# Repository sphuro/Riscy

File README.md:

# RISCY

I am bulding a devboard using esp32-c3 for risc 5 architechture.

## Module

- esp32-c3 02 :-
  `https://robu.in/product/espressif-esp32-c3-wroom-02-n4-module/`

## USB slave to UART

- usb to uart link x1:-
  `https://robu.in/product/ft231xs-usb-to-full-handshake-uart-ic/`
- usb c 3.1 female buy link x1 :-
  `https://sharvielectronics.com/product/16-pin-c-type-usb-connector-smd-package/`

### Automatic Bootloader mechanism

- here is the blog covering this topic:
  `https://medium.com/@kazutaka.yoshinaga/esp32-understanding-the-automatic-boot-loader-mechanism-and-truth-table-68c4dcfd081b`
- BJT link x2 :-
  `https://robu.in/product/mmbt2222-npn-transistor-pack-of-15/`

## Reset and Boot buttons

### tact-switch-tvbp06-6-0x3-5mm

- 4 pin tactile switch x2 :-
  `https://sharvielectronics.com/product/6x6x6mm-4-pin-smd-push-button-switch-black-smd-package/?srsltid=AfmBOoqkUntN9e5Ccbb3nGcXEwSu-7Jxecq2lp09xIixMuHtoX-pbkdE`

## Programable LED

- link to buy x1 each:-
  - `https://robu.in/product/1206-surface-mount-led-white-50-pcs/`
  - `https://robu.in/product/0805-surface-mount-led-green-50-pcs/`
  - `https://robu.in/product/1210-surface-mount-led-red-50-pcs/`

## Voltage Regulator

- link to buy x1:-
  - `https://robu.in/product/ams1117-3-3v-1a-sot-223-voltage-regulator-ic-pack-of-5-ics/?gad_source=1&gclid=Cj0KCQiAhvK8BhDfARIsABsPy4iSbVYHEwlP9KEBU2B-lCpn-yx6If_Pfp03lKlFopRlRfcGBhBD0BAaAo5wEALw_wcB`

## Schematics

## Capacitors

- 47 pf (1206) x2
  `https://robu.in/product/1206cg470j102nt-fh-smd-multilayer-ceramic-capacitor-47-pf-1k-v-1206-3216-metric-%C2%B1-5-c0g-np0/`

- 1uf (0805) x1
  `https://robu.in/product/1uf-1000nf-50v-capacitor-0805-smd-package-pack-of-10/?gad_source=1&gclid=CjwKCAiAqfe8BhBwEiwAsne6gRW89rA8-Swm024kPMmwT7c9DuGJLPZeQFsVlMFR-OqpyiHtYQ1T4hoC8iMQAvD_BwE`

- 0.1uf (0603) x4
  `https://robu.in/product/0-1uf-capacitor-smdc-0603/?gad_source=1&gclid=CjwKCAiAqfe8BhBwEiwAsne6gWn9uzvhnW72vBLiLfLgH6g2IBu4aXkYyNnVniyPnGsfjDwM305cGxoC8nkQAvD_BwE`
- 10uf (0805) x1
  `https://robu.in/product/10uf-10000nf-25-v-capacitor-0805-smd-package-pack-of-10/?gad_source=1&gclid=CjwKCAiAqfe8BhBwEiwAsne6gSNCd9WapUePWtNVtayLgPHIMiImB_SQO5EiwIjBxiPgrBeaZvYwxxoCuBgQAvD_BwE`

- 22uf (0805) x2
  `https://robu.in/product/yageo-22uf-25v-electrolytic-capacitor-5-x-11mm/?gad_source=1&gclid=CjwKCAiAqfe8BhBwEiwAsne6gWyHPdNbx2DJMTqJMZTA1229QODbWIoOOmdcEkEg3BOqxQL2i1x2ehoCttgQAvD_BwE`

## Resistors

- 10k (1206) x3
  `https://robu.in/product/yageo-10k-ohm-1-4w-1206-surface-mount-chip-resistor-pack-of-50/?gad_source=1&gclid=CjwKCAiAqfe8BhBwEiwAsne6gZWv9w5e9PMNmgXxTNiYDh80E5rCTzmXLJArUMoy2vFAzwSFBDGwHRoCKAUQAvD_BwE`
- 2k (0603) x1
  `https://robu.in/product/rc0603fr-072kl-yageo-res-thick-film-0603-2k-ohm-1-0-1w1-10w-%C2%B1100ppm-c-pad-smd-t-r/?gad_source=1&gclid=CjwKCAiAqfe8BhBwEiwAsne6gWDPpM3FZ68ny4cKiBX4H2pzpEQgQKrVqhm_9OjcrVDXVOdlWZfx0RoCqCEQAvD_BwE`
- 5.1k (1206) x1
  `https://robu.in/product/rc1206fr-075k1l-yageo-res-thick-film-1206-5-1k-ohm-1-0-25w1-4w-%C2%B1100ppm-c-pad-smd-t-r/?gad_source=1&gclid=CjwKCAiAqfe8BhBwEiwAsne6gRqt6TucMgg01SNZ5VyACSfpWdVqewY8vab5gWvl6FbrrHuYexlRzxoCukMQAvD_BwE`
- 22k (1206) x3
  `https://robu.in/product/22k-ohm-1-4w-1206-surface-mount-chip-resistor-pack-of-100/?gad_source=1&gclid=CjwKCAiAqfe8BhBwEiwAsne6gS6hBlgg2iVJp858rXo21lLIIVadU-xK-fzI3kwSm3MWMYYFXDwUsBoCjh4QAvD_BwE`
- 27 (0805) x2
  `https://robu.in/product/rc0805fr-0727rl-yageo-smd-chip-resistor-27-ohm-%C2%B1-1-125-mw-0805-2012-metric-thick-film-general-purpose/`
- 1 (1206) x2
  `https://robu.in/product/1-ohm-1-4w-1206-surface-mount-chip-resistor-pack-of-100/?gad_source=1&gclid=CjwKCAiAqfe8BhBwEiwAsne6gYzLEAPAPqUGiqb02MYLoErwIDmVYmgq0LpQvgXpQUw6lDAnweQhTRoCmqYQAvD_BwE`

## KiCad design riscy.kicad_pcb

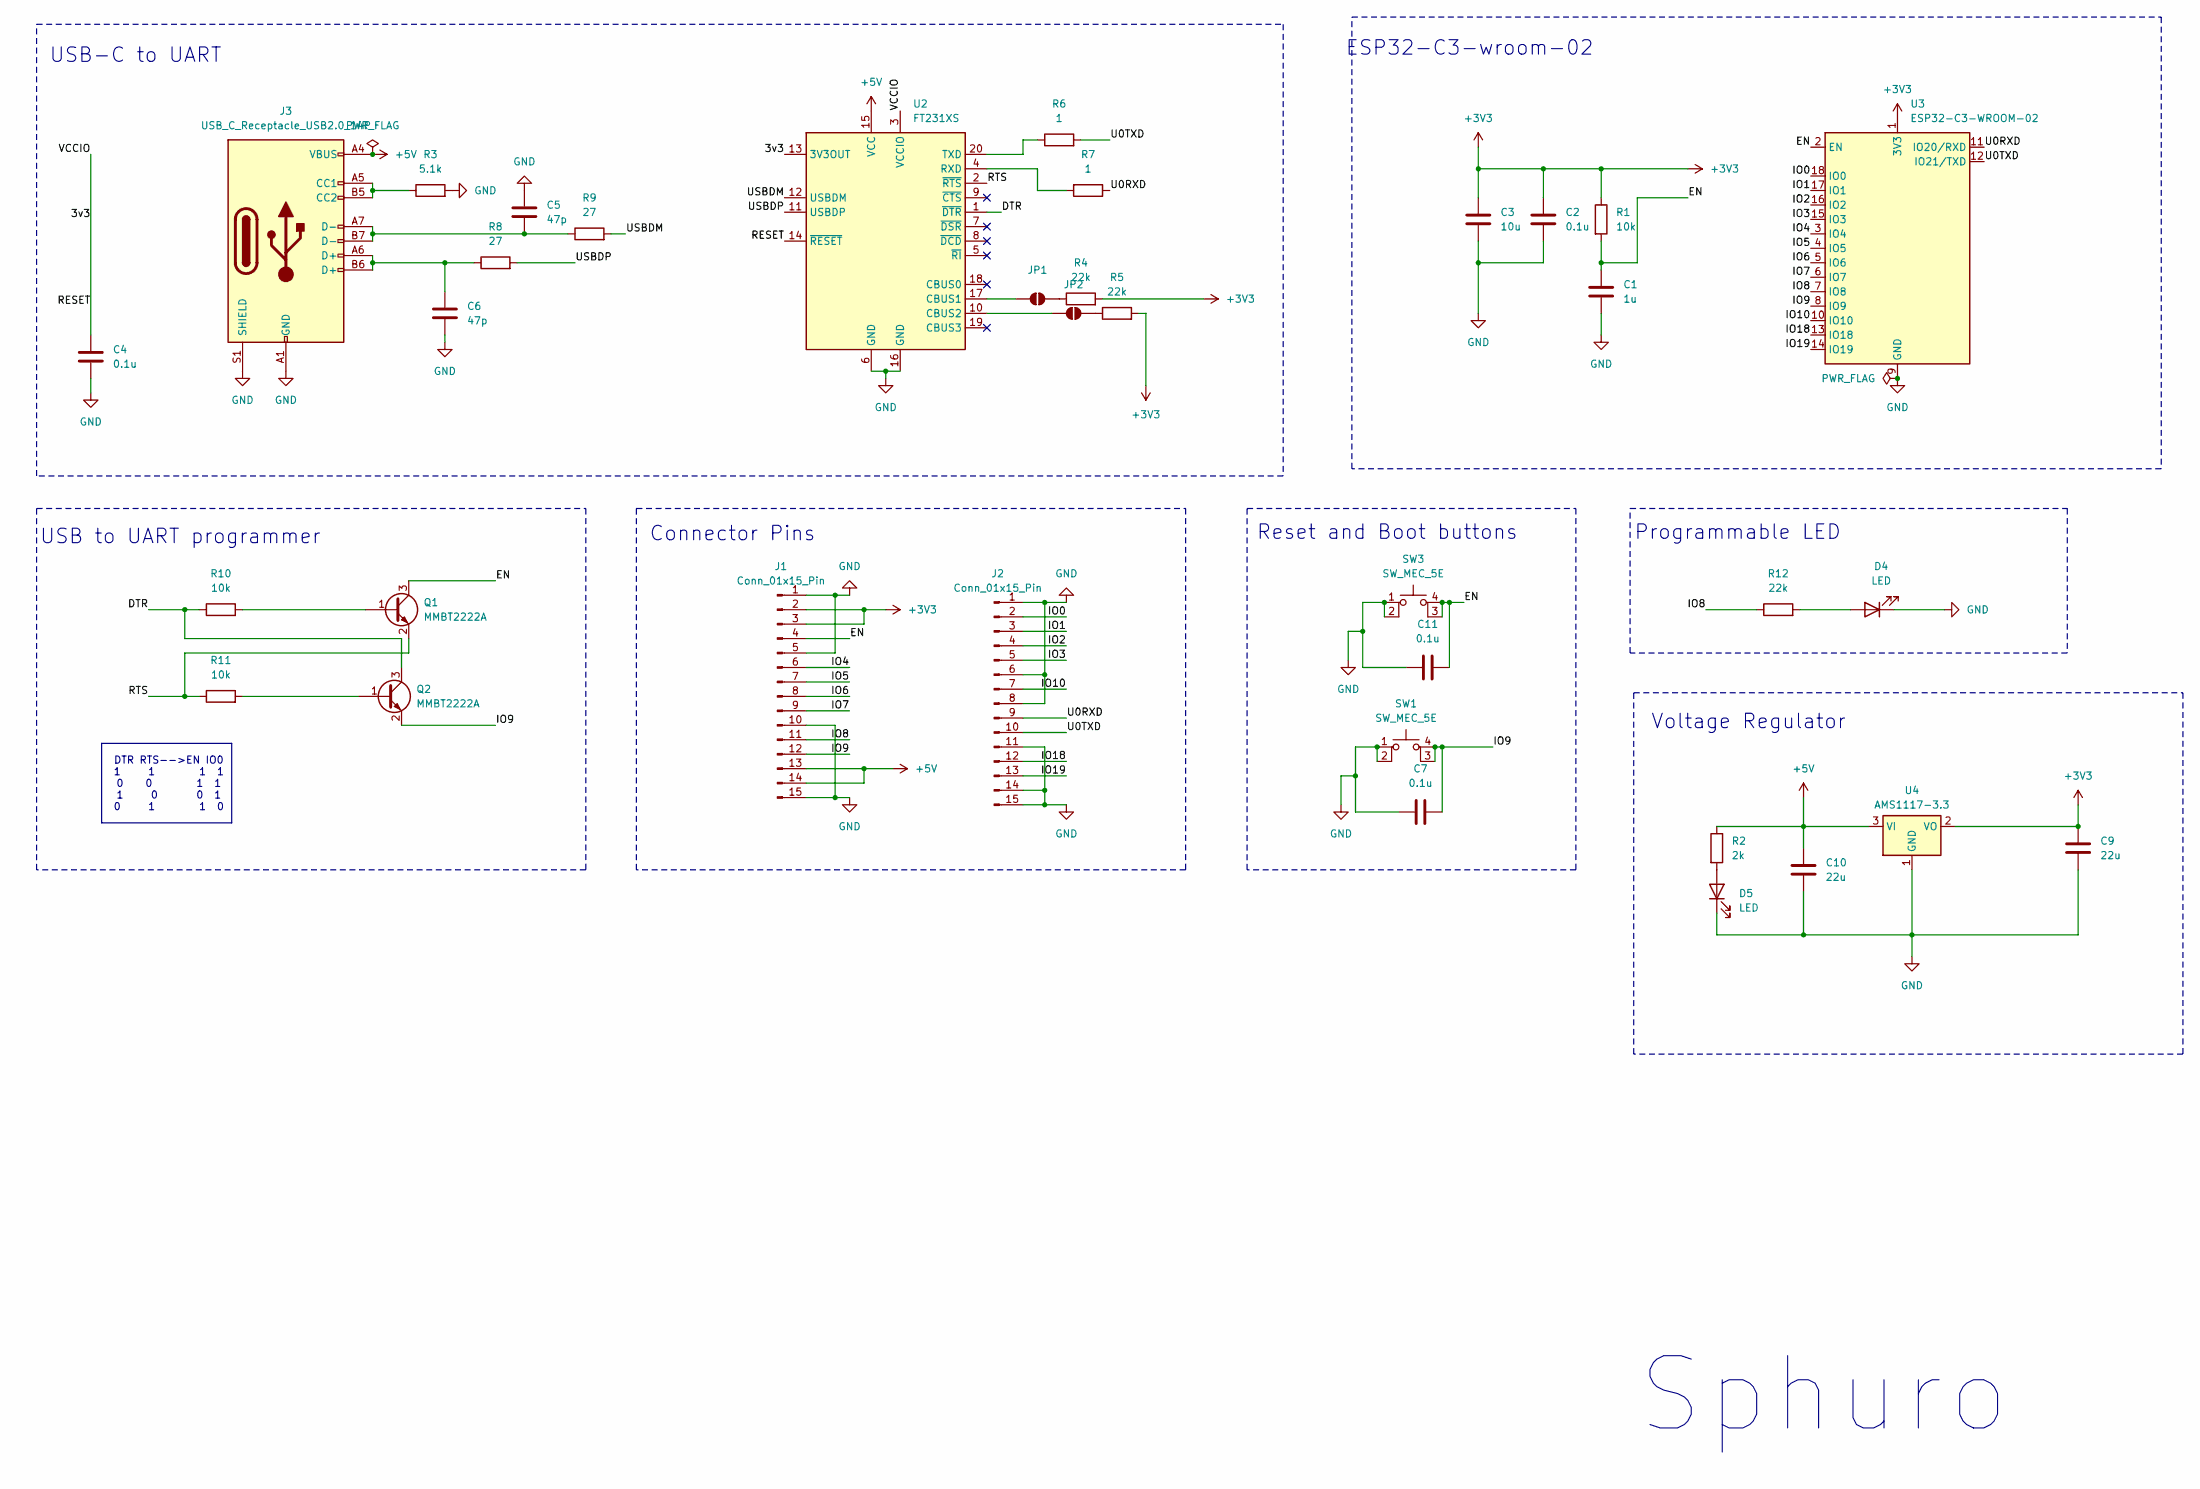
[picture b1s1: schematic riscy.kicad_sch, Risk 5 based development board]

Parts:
C1: 1u; C_0805_2012Metric
C2, C4, C7, C11: 0.1u; C_0603_1608Metric
C3: 10u; C_1206_3216Metric
C5, C6: 47p; C_1206_3216Metric
C9, C10: 22u; C_0805_2012Metric
D4: LED; LED_1206_3216Metric
D5: LED; LED_0805_2012Metric
J1, J2: Conn_01x15_Pin; PinHeader_1x15_P2.54mm_Vertical
J3: USB_C_Receptacle_USB2.0_14P; USB_C_Receptacle_GCT_USB4105-xx-A_16P_TopMnt_Horizontal
JP1, JP2: SolderJumper-2_P1.3mm_Open_RoundedPad1.0x1.5mm
Q1, Q2: MMBT2222A; SOT-23
R1, R10, R11: 10k; R_1206_3216Metric
R2: 2k; R_0603_1608Metric
R3: 5.1k; R_1206_3216Metric
R4, R5, R12: 22k; R_1206_3216Metric
R6, R7: 1; R_1206_3216Metric
R8, R9: 27; R_0805_2012Metric
SW1, SW3: SW_MEC_5E; SW_1825910-6-4
U2: FT231XS; SSOP-20_3.9x8.7mm_P0.635mm
U3: ESP32-C3-WROOM-02
U4: AMS1117-3.3; SOT-223-3_TabPin2

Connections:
+3V3: C2.1, C3.1, C9.1, J1.2, J1.3, R1.1, R4.2, R5.2, U3.1 (3V3), U4.2 (VO)
+5V: C10.1, J1.13, J1.14, J3.A4 (VBUS), J3.A9 (VBUS), J3.B4 (VBUS), J3.B9 (VBUS), R2.1, U2.15 (VCC), U4.3 (VI)
/3v3: C4.1, U2.3 (VCCIO), U2.13 (3V3OUT), U2.14 (~RESET)
/DTR: Q2.3 (C), R10.1, U2.1 (~DTR)
/EN: C1.1, C11.2, J1.4, Q1.3 (C), R1.2, SW3.3 (K), SW3.4 (A), U3.2 (EN)
/IO0: J2.2, U3.18 (IO0)
/IO1: J2.3, U3.17 (IO1)
/IO2: J2.4, U3.16 (IO2)
/IO3: J2.5, U3.15 (IO3)
/IO4: J1.6, U3.3 (IO4)
/IO5: J1.7, U3.4 (IO5)
/IO6: J1.8, U3.5 (IO6)
/IO7: J1.9, U3.6 (IO7)
/IO8: J1.11, R12.1, U3.7 (IO8)
/IO9: C7.2, J1.12, Q2.2 (E), SW1.3 (K), SW1.4 (A), U3.8 (IO9)
/IO10: J2.7, U3.10 (IO10)
/IO18: J2.12, U3.13 (IO18)
/IO19: J2.13, U3.14 (IO19)
/RTS: Q1.2 (E), R11.1, U2.2 (~RTS)
/U0RXD: J2.9, R7.1, U3.11 (IO20/RXD)
/U0TXD: J2.10, R6.2, U3.12 (IO21/TXD)
/USBDM: R9.2, U2.12 (USBDM)
/USBDP: R8.2, U2.11 (USBDP)
GND: C1.2, C2.2, C3.2, C4.2, C5.1, C6.2, C7.1, C9.2, C10.2, C11.1, D4.1 (K), D5.1 (K), J1.1, J1.5, J1.10, J1.15, J2.1, J2.6, J2.8, J2.11, J2.14, J2.15, J3.A1 (GND), J3.A12 (GND), J3.B1 (GND), J3.B12 (GND), J3.S1 (SHIELD), R3.2, SW1.1, SW1.2, SW3.1, SW3.2, U2.6 (GND), U2.16 (GND), U3.9 (GND), U3.19 (GND), U4.1 (GND)
unnamed: C5.2, J3.A7 (D-), J3.B7 (D-), R9.1
unnamed: C6.1, J3.A6 (D+), J3.B6 (D+), R8.1
unnamed: D4.2 (A), R12.2
unnamed: D5.2 (A), R2.2
unnamed: J3.A5 (CC1), J3.B5 (CC2), R3.1
unnamed: JP1.1 (A), U2.17 (CBUS1)
unnamed: JP1.2 (B), R4.1
unnamed: JP2.1 (A), R5.1
unnamed: JP2.2 (B), U2.10 (CBUS2)
unnamed: Q1.1 (B), R10.2
unnamed: Q2.1 (B), R11.2
unnamed: R7.2, U2.4 (RXD)
unnamed: R6.1, U2.20 (TXD)

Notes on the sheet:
USB-C to UART
DTR RTS-->EN IO0 1 1 1 1 0 0 1 1 1 0 0 1 0 1 1 0
Voltage Regulator
Reset and Boot buttons
Sphuro
Connector Pins
ESP32-C3-wroom-02
Programmable LED
USB to UART programmer

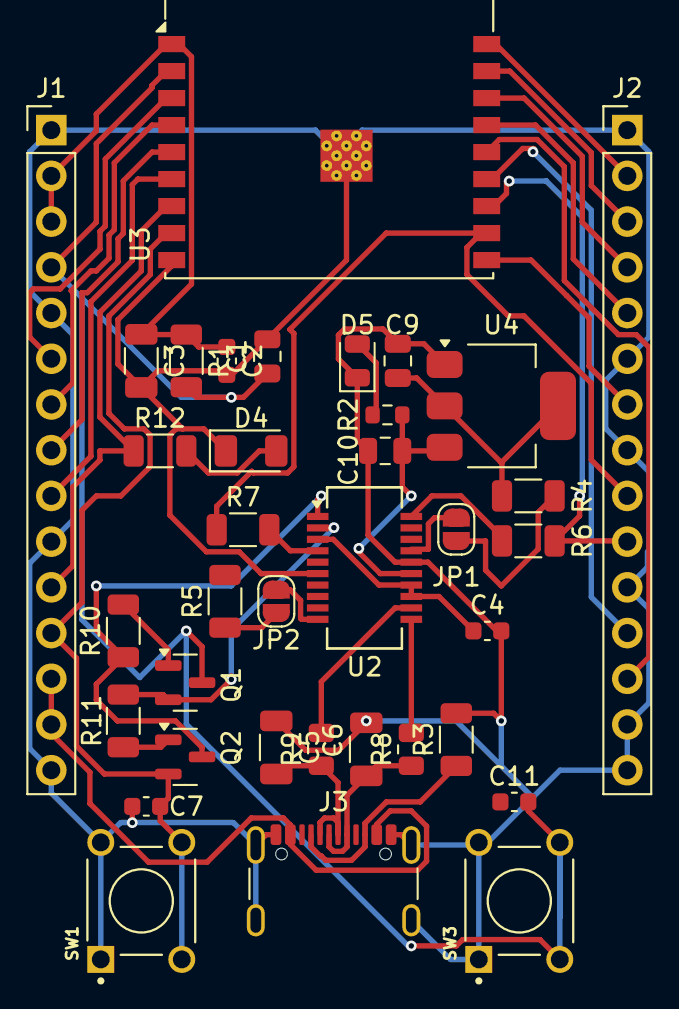
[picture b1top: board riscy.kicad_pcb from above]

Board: 2 copper layers, 36 parts (0 on the bottom side), 37 nets.

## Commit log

2025-01-26 added kicad schem
2025-01-26 added README
2025-01-30 updated schematics
2025-01-30 schematic near compleation
2025-02-01 completed schematic
2025-02-01 schematic image
2025-02-01 assigned some footprints
2025-02-02 updated schematic
2025-02-03 fixed issues in schematicss
2025-02-03 updated schematicss
2025-02-03 added schematic photo
2025-02-03 added switch footprints
2025-02-03 shcematic completed now to the pcb design:)
2025-02-04 pcb design started
2025-02-04 Update LICENSE
2025-02-06 updated pcb
2025-02-09 changed schematics
2025-02-09 changed capacitor footprint
2025-02-18 changed
2025-03-04 making pcb
2025-03-24 updated design
2025-05-09 added screenshots of pcb design
